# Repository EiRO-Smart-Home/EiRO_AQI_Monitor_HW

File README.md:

# AQI monitor

This project is a developement board based on a MGM260PD32VNA2 Module from SiliconLabs, SEN5x series sensors and with support for ePaper and other SPI based displays.
This board has been realized for the lack of available options that would satisfy our need in therms of a good air quality sensor. As for most commercial solutions are expensive, or they lack some features, such as Matter connectivity or some types of enviromental sensing. Most of the time they detect only PM2.5 and not PM10 and some do not include VOCs. 
Our targets of sensing values are the followings.
- Temperature
- Humidity
- PM 1.0, PM 2.5, PM 4, PM10
- VOC (index)
- CO2 
- NOx
- Formaldehyde 
- Overall AQI index (calculated)
  
Most of the sensing can be done using SEN55 and two addittional sensors for Formaldehyde and CO2. A SEN69C can also be used, but VCC on the connector is 5V and newer SEN6x are 3.3V powered, so the board has to be modified.

An advantage of using Matter as the default connectivity standard, is the ease of integrating it in any smart home (with also a Thread Border Router). There is no need for vendor specific applications, as all the data will be managed by Matter. This means there is no need for subscription and the device is completely local.

## Hardware Features

 - MGM260 SoM
   * BLE 5.4 Support 
   * Zigbee 3.0 and up
   * OpenThread
   * ARM Cortex M33 @ 80 MHz
   * 3.2MB Flash + 512kB RAM
   * Matrix Vector Processor for ML
 - SHT41 Temp. and Humidity Sensor
 - JTAG-SWD-9 connector
 - SPI expansion 4x2 1.27mm pitch
 - SPI connection for external display 
 - I2C expansion for external SEN5x series sensor node
 - USB-C for power and serial communication

## PICTURES

## LICENSE

Copyright Francesco Salmaso - EiRO.tech 2025-2026
This source describes Open Hardware and is licensed under the CERN-
OHL-S v2.
You may redistribute and modify this source and make products using it
under the terms of the CERN-OHL-S v2
(https://ohwr.org/cern ohl s v2.txt ).
This source is distributed WITHOUT ANY EXPRESS OR IMPLIED
WARRANTY, INCLUDING OF MERCHANTABILITY, SATISFACTORY
QUALITY AND FITNESS FOR A PARTICULAR PURPOSE. Please see
the CERN-OHL-S v2 for applicable conditions.
Source location: https://github.com/EiRO-Smart-Home/EiRO_AQI_Monitor_HW
As per CERN-OHL-S v2 section 4, should You produce hardware based
on this source, You must where practicable maintain the Source Location
visible on the external case of the EiRO AQI Monitor or other products you make using
this source.

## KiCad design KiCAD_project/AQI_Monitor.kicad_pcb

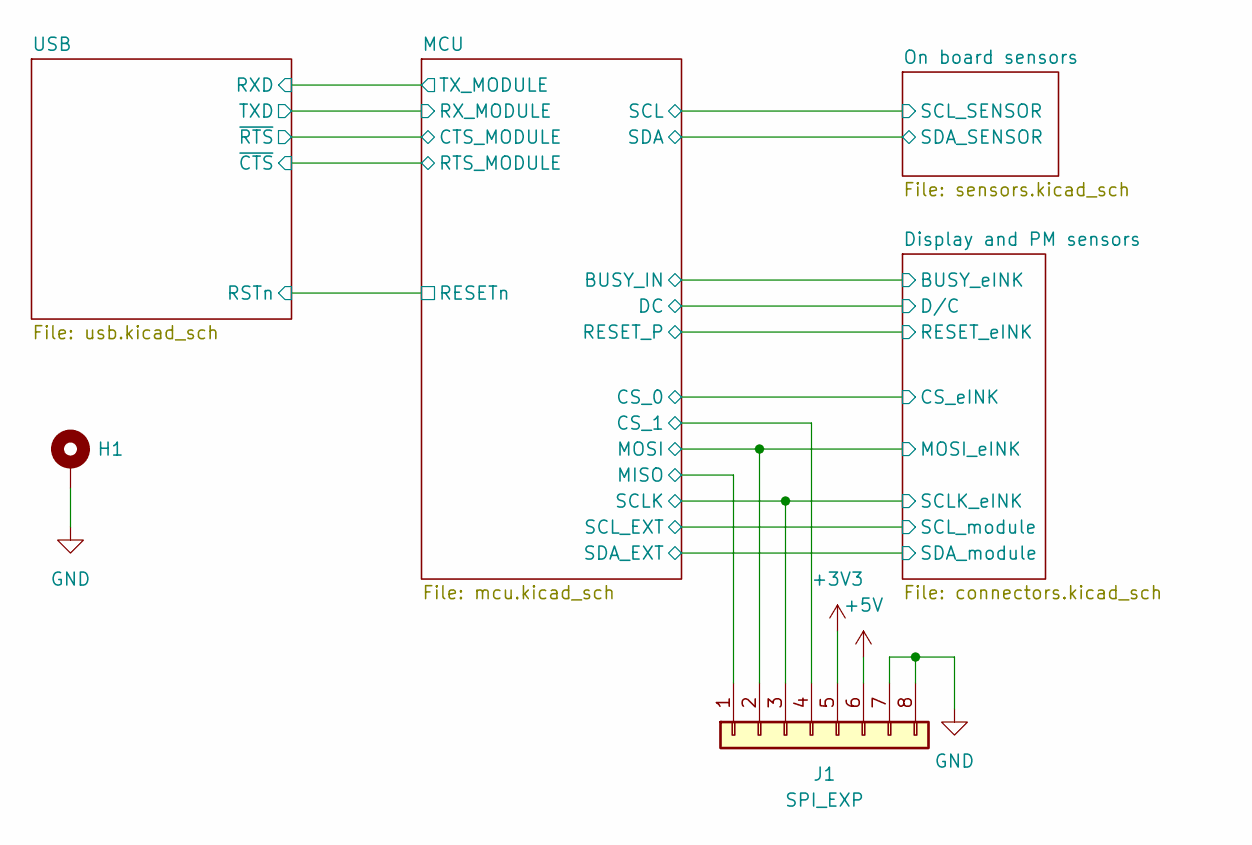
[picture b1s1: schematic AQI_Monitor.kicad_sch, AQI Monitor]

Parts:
H1: MountingHole_Pad; MountingHole_2.7mm_M2.5_DIN965_Pad
J1: SPI_EXP; PinHeader_2x04_P1.27mm_Vertical_SMD

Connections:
+3V3: J1.5; also elsewhere on the board
+5V: J1.6; also elsewhere on the board
/Display and PM sensors/MOSI_eINK: J1.2; also elsewhere on the board
/Display and PM sensors/SCLK_eINK: J1.3; also elsewhere on the board
/MCU/CS_1: J1.4; also elsewhere on the board
/MCU/MISO: J1.1; also elsewhere on the board
GND: H1.1, J1.7, J1.8; also elsewhere on the board

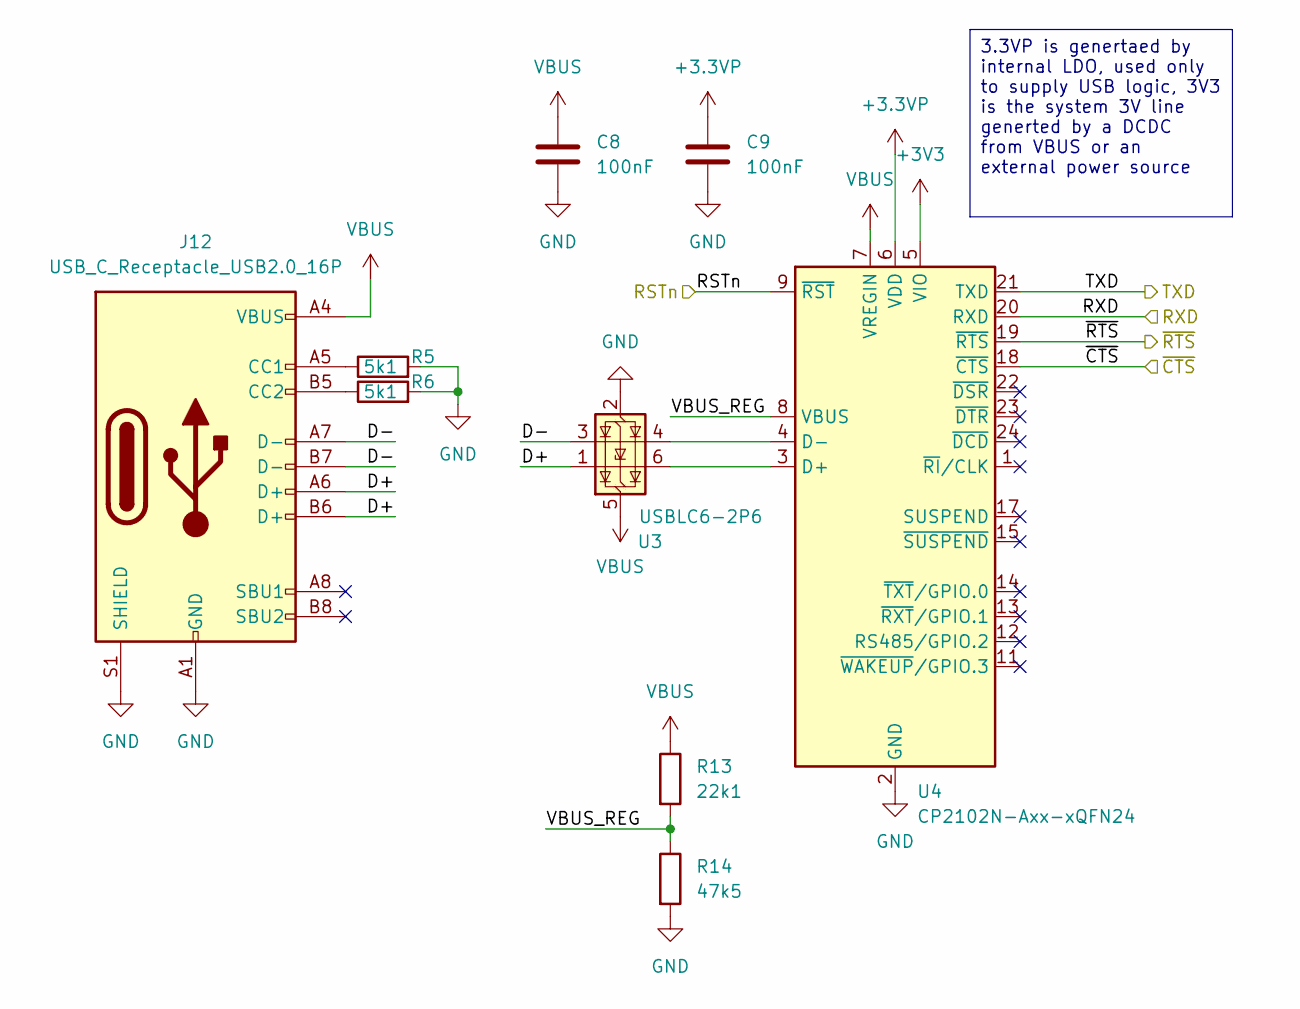
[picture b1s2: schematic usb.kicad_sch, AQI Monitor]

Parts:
C8, C9: 100nF; C_0603_1608Metric_Pad1.08x0.95mm_HandSolder
J12: USB_C_Receptacle_USB2.0_16P; USB_C_Receptacle_JAE_DX07S016JA1R1500
R5, R6: 5k1; R_0603_1608Metric_Pad0.98x0.95mm_HandSolder
R13: 22k1; R_0603_1608Metric_Pad0.98x0.95mm_HandSolder
R14: 47k5; R_0603_1608Metric_Pad0.98x0.95mm_HandSolder
U3: USBLC6-2P6; SOT-666
U4: CP2102N-Axx-xQFN24; QFN-24-1EP_4x4mm_P0.5mm_EP2.6x2.6mm

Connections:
+3.3VP: C9.1, U4.6 (VDD)
+3V3: U4.5 (VIO); also elsewhere on the board
/MCU/CTS_MODULE: U4.19 (~RTS); also elsewhere on the board
/MCU/RESETn: U4.9 (~RST); also elsewhere on the board
/MCU/RTS_MODULE: U4.18 (~CTS); also elsewhere on the board
/MCU/RX_MODULE: U4.21 (TXD); also elsewhere on the board
/MCU/TX_MODULE: U4.20 (RXD); also elsewhere on the board
/USB/D+: J12.A6 (D+), J12.B6 (D+), U3.1 (I/O1)
/USB/D-: J12.A7 (D-), J12.B7 (D-), U3.3 (I/O2)
/USB/VBUS_REG: R13.2, R14.1, U4.8 (VBUS)
GND: C8.2, C9.2, J12.A1 (GND), J12.A12 (GND), J12.B1 (GND), J12.B12 (GND), J12.S1 (SHIELD), R5.2, R6.2, R14.2, U3.2 (GND), U4.2 (GND), U4.25 (GND); also elsewhere on the board
unnamed: J12.A5 (CC1), R5.1
unnamed: J12.B5 (CC2), R6.1
unnamed: U3.6 (I/O1), U4.3 (D+)
unnamed: U3.4 (I/O2), U4.4 (D-)
VBUS: C8.1, J12.A4 (VBUS), J12.A9 (VBUS), J12.B4 (VBUS), J12.B9 (VBUS), R13.1, U3.5 (VBUS), U4.7 (VREGIN); also elsewhere on the board

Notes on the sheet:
3.3VP is genertaed by internal LDO, used only to supply USB logic, 3V3 is the system 3V line generted by a DCDC from VBUS or an external power source

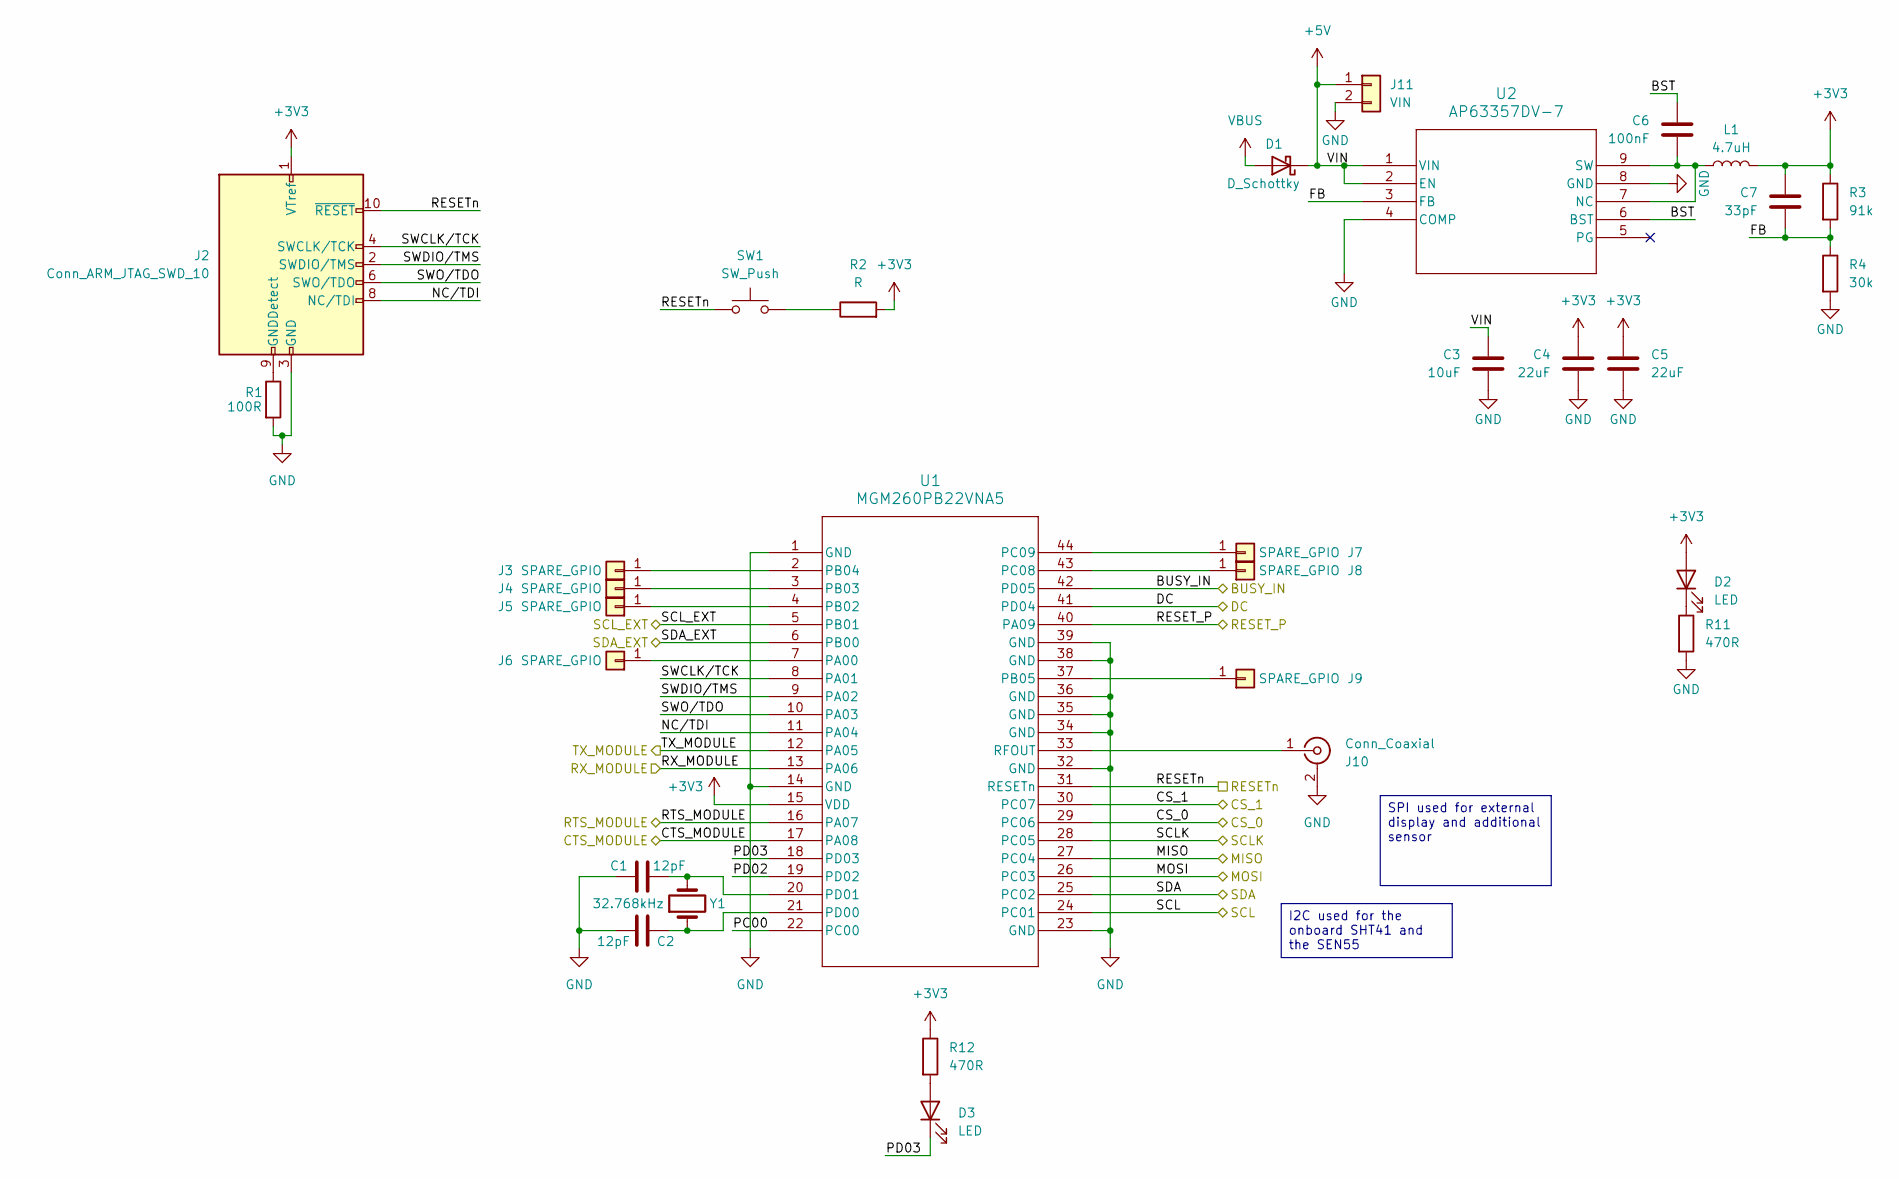
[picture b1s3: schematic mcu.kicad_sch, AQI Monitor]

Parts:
C1, C2: 12pF; C_0603_1608Metric_Pad1.08x0.95mm_HandSolder
C3: 10uF; C_0805_2012Metric_Pad1.18x1.45mm_HandSolder
C4, C5: 22uF; C_0805_2012Metric_Pad1.18x1.45mm_HandSolder
C6: 100nF; C_0603_1608Metric_Pad1.08x0.95mm_HandSolder
C7: 33pF; C_0603_1608Metric_Pad1.08x0.95mm_HandSolder
D1: D_Schottky; D_SMA
D2, D3: LED; D_0603_1608Metric_Pad1.05x0.95mm_HandSolder
J2: Conn_ARM_JTAG_SWD_10; PinHeader_2x05_P1.27mm_Vertical_SMD
J3, J4, J5, J6, J7, J8, J9: SPARE_GPIO; SolderWirePad_1x01_SMD_1x2mm
J10: Conn_Coaxial; U.FL_Hirose_U.FL-R-SMT-1_Vertical
J11: VIN; PinSocket_1x02_P2.54mm_Vertical
L1: 4.7uH; L_1210_3225Metric_Pad1.42x2.65mm_HandSolder
R1: 100R; R_0603_1608Metric_Pad0.98x0.95mm_HandSolder
R2: R; R_0603_1608Metric_Pad0.98x0.95mm_HandSolder
R3: 91k; R_0603_1608Metric_Pad0.98x0.95mm_HandSolder
R4: 30k; R_0603_1608Metric_Pad0.98x0.95mm_HandSolder
R11, R12: 470R; R_0603_1608Metric_Pad0.98x0.95mm_HandSolder
SW1: SW_Push; SW_SPST_PTS810
U1: MGM260PB22VNA5; MODULE_xGM260P_SIL
U2: AP63357DV-7; V-DFN3020-13_DIO
Y1: 32.768kHz; Crystal_SMD_MicroCrystal_CC8V-T1A-2Pin_2.0x1.2mm_HandSolder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

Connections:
+3V3: C4.1, C5.1, C7.1, D2.2 (A), J2.1 (VTref), L1.2, R2.2, R3.1, R12.1, U1.15 (VDD); also elsewhere on the board
+5V: C3.1, D1.1 (K), J11.1, U2.1 (VIN), U2.2 (EN); also elsewhere on the board
/Display and PM sensors/BUSY_eINK: U1.42 (PD05); also elsewhere on the board
/Display and PM sensors/CS_eINK: U1.29 (PC06); also elsewhere on the board
/Display and PM sensors/D/C: U1.41 (PD04); also elsewhere on the board
/Display and PM sensors/MOSI_eINK: U1.26 (PC03); also elsewhere on the board
/Display and PM sensors/RESET_eINK: U1.40 (PA09); also elsewhere on the board
/Display and PM sensors/SCLK_eINK: U1.28 (PC05); also elsewhere on the board
/Display and PM sensors/SCL_module: U1.5 (PB01); also elsewhere on the board
/Display and PM sensors/SDA_module: U1.6 (PB00); also elsewhere on the board
/MCU/BST: C6.1, U2.6 (BST)
/MCU/CS_1: U1.30 (PC07); also elsewhere on the board
/MCU/CTS_MODULE: U1.17 (PA08); also elsewhere on the board
/MCU/FB: C7.2, R3.2, R4.1, U2.3 (FB)
/MCU/MISO: U1.27 (PC04); also elsewhere on the board
/MCU/PC00: U1.22 (PC00)
/MCU/PD02: U1.19 (PD02)
/MCU/PD03: D3.1 (K), U1.18 (PD03)
/MCU/RESETn: J2.10 (~RESET), SW1.1, U1.31 (RESETn); also elsewhere on the board
/MCU/RTS_MODULE: U1.16 (PA07); also elsewhere on the board
/MCU/RX_MODULE: U1.13 (PA06); also elsewhere on the board
/MCU/SCL: U1.24 (PC01); also elsewhere on the board
/MCU/SDA: U1.25 (PC02); also elsewhere on the board
/MCU/TX_MODULE: U1.12 (PA05); also elsewhere on the board
GND: C1.1, C2.2, C3.2, C4.2, C5.2, J2.3 (GND), J2.5 (GND), J10.2 (Ext), J11.2, R1.2, R4.2, R11.2, U1.1 (GND), U1.14 (GND), U1.23 (GND), U1.32 (GND), U1.34 (GND), U1.35 (GND), U1.36 (GND), U1.38 (GND), U1.39 (GND), U2.4 (COMP), U2.8 (GND); also elsewhere on the board
unnamed: D2.1 (K), R11.1
unnamed: D3.2 (A), R12.2
unnamed: J2.9 (GNDDetect), R1.1
unnamed: J3.1, U1.2 (PB04)
unnamed: J4.1, U1.3 (PB03)
unnamed: J5.1, U1.4 (PB02)
unnamed: J6.1, U1.7 (PA00)
unnamed: J7.1, U1.44 (PC09)
unnamed: J8.1, U1.43 (PC08)
unnamed: J9.1, U1.37 (PB05)
unnamed: J10.1 (In), U1.33 (RFOUT)
unnamed: R2.1, SW1.2
unnamed: C2.1, U1.21 (PD00), Y1.1
unnamed: C1.2, U1.20 (PD01), Y1.2
unnamed: C6.2, L1.1, U2.7 (NC), U2.9 (SW)
VBUS: D1.2 (A); also elsewhere on the board

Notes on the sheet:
I2C used for the onboard SHT41 and the SEN55
SPI used for external display and additional sensor

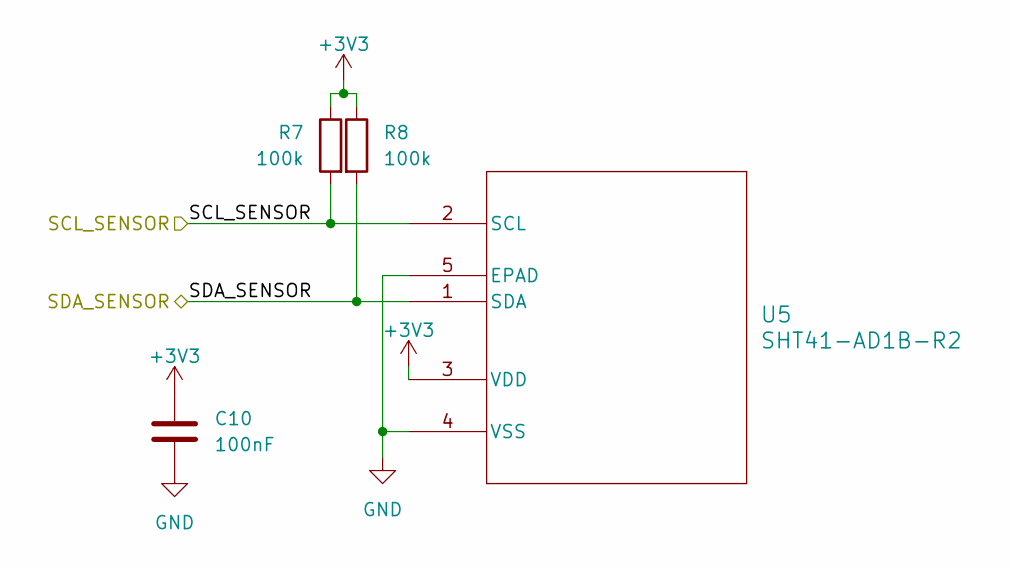
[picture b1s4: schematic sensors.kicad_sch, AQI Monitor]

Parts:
C10: 100nF; C_0603_1608Metric_Pad1.08x0.95mm_HandSolder
R7, R8: 100k; R_0603_1608Metric_Pad0.98x0.95mm_HandSolder
U5: SHT41-AD1B-R2; DFN4_SHT41_SEN

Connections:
+3V3: C10.1, R7.1, R8.1, U5.3 (VDD); also elsewhere on the board
/MCU/SCL: R7.2, U5.2 (SCL); also elsewhere on the board
/MCU/SDA: R8.2, U5.1 (SDA); also elsewhere on the board
GND: C10.2, U5.4 (VSS), U5.5 (EPAD); also elsewhere on the board

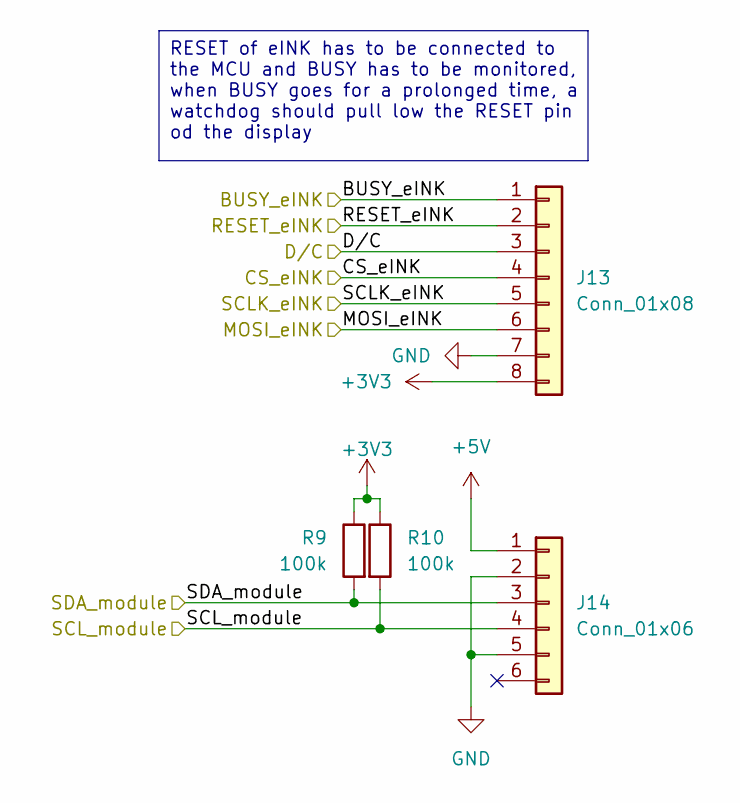
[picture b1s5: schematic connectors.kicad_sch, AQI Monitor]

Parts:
J13: Conn_01x08; JST_GH_BM08B-GHS-TBT_1x08-1MP_P1.25mm_Vertical
J14: Conn_01x06; JST_GH_BM06B-GHS-TBT_1x06-1MP_P1.25mm_Vertical
R9, R10: 100k; R_0603_1608Metric_Pad0.98x0.95mm_HandSolder

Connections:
+3V3: J13.8, R9.1, R10.1; also elsewhere on the board
+5V: J14.1; also elsewhere on the board
/Display and PM sensors/BUSY_eINK: J13.1; also elsewhere on the board
/Display and PM sensors/CS_eINK: J13.4; also elsewhere on the board
/Display and PM sensors/D/C: J13.3; also elsewhere on the board
/Display and PM sensors/MOSI_eINK: J13.6; also elsewhere on the board
/Display and PM sensors/RESET_eINK: J13.2; also elsewhere on the board
/Display and PM sensors/SCLK_eINK: J13.5; also elsewhere on the board
/Display and PM sensors/SCL_module: J14.4, R10.2; also elsewhere on the board
/Display and PM sensors/SDA_module: J14.3, R9.2; also elsewhere on the board
GND: J13.7, J14.2, J14.5; also elsewhere on the board

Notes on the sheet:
RESET of eINK has to be connected to the MCU and BUSY has to be monitored, when BUSY goes for a prolonged time, a watchdog should pull low the RESET pin od the display

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
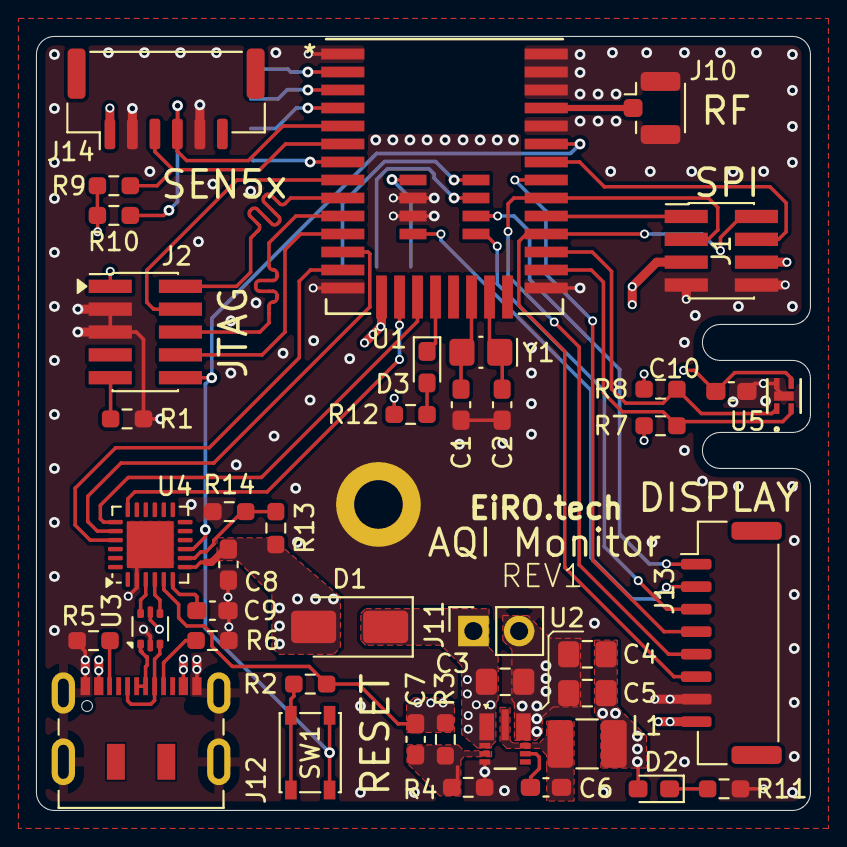
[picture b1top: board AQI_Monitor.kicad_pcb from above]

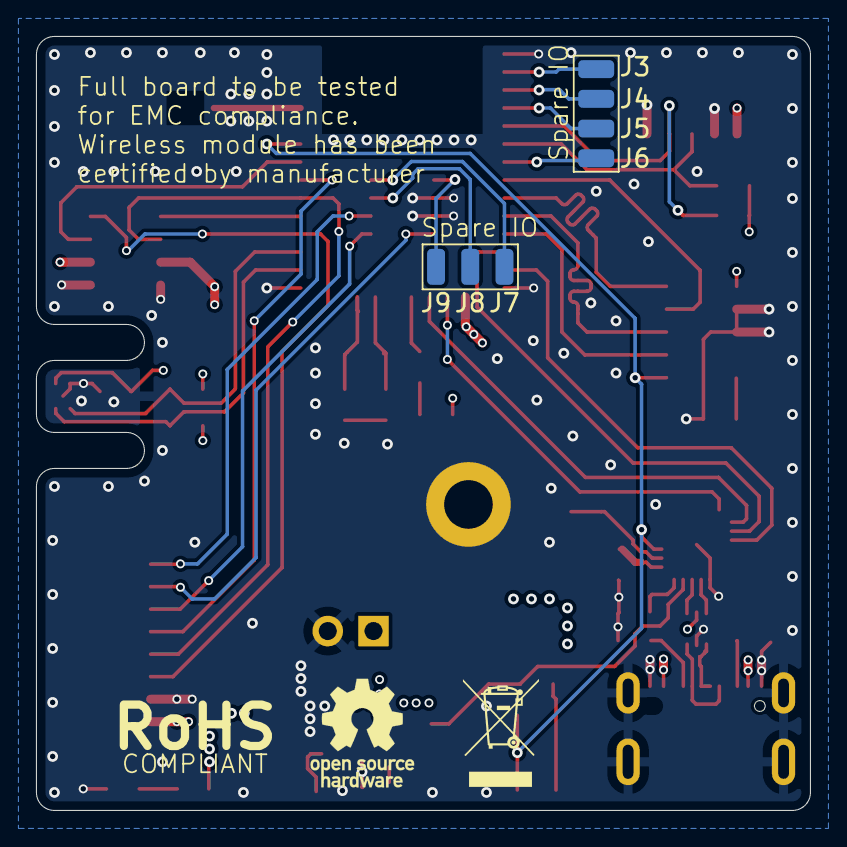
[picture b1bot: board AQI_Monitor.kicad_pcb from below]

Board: 4 copper layers, 43.0 x 43.0 mm, 50 parts (7 on the bottom side), 51 nets.

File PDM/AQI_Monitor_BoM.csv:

Id;Designator;Footprint;Quantity;Designation;Supplier and ref;;
1;R14;R_0603_1608Metric_Pad0.98x0.95mm_HandSolder;1;47k5;;v;x
2;C7;C_0603_1608Metric_Pad1.08x0.95mm_HandSolder;1;33pF;;v;x
3;R6,R5;R_0603_1608Metric_Pad0.98x0.95mm_HandSolder;2;5k1;;v;x
4;C3;C_0805_2012Metric_Pad1.18x1.45mm_HandSolder;1;10uF;;v;x
5;J14;JST_GH_BM06B-GHS-TBT_1x06-1MP_P1.25mm_Vertical;1;Conn_01x06;;ok;
6;R12,R11;R_0603_1608Metric_Pad0.98x0.95mm_HandSolder;2;470R;;v;x
7;C10,C8,C9,C6;C_0603_1608Metric_Pad1.08x0.95mm_HandSolder;4;100nF;;v;x
8;C1,C2;C_0603_1608Metric_Pad1.08x0.95mm_HandSolder;2;12pF;;v;x
9;D1;D_SMA;1;D_Schottky;;v;x
10;U4;QFN-24-1EP_4x4mm_P0.5mm_EP2.6x2.6mm;1;CP2102N-Axx-xQFN24;;v;x
11;SW1;SW_SPST_PTS810;1;SW_Push;;v;x
12;R8,R7,R9,R10;R_0603_1608Metric_Pad0.98x0.95mm_HandSolder;4;100k;;v;x
13;C4,C5;C_0805_2012Metric_Pad1.18x1.45mm_HandSolder;2;22uF;;v;x
14;J12;USB_C_Receptacle_JAE_DX07S016JA1R1500;1;USB_C_Receptacle_USB2.0_16P;;ok;
15;U1;MODULE_xGM260P_SIL;1;MGM260PB22VNA5;;v;xxx
16;J1;PinHeader_2x04_P1.27mm_Vertical_SMD;1;SPI_EXP;;v;x
17;R1;R_0603_1608Metric_Pad0.98x0.95mm_HandSolder;1;100R;;v;x
18;D3,D2;D_0603_1608Metric_Pad1.05x0.95mm_HandSolder;2;LED;;v;xx
19;R3;R_0603_1608Metric_Pad0.98x0.95mm_HandSolder;1;91k;;v;x
20;U2;V-DFN3020-13_DIO;1;AP63357DV-7;;ok;
21;J11;PinSocket_1x02_P2.54mm_Vertical;1;VIN;;ok;
22;J13;JST_GH_BM08B-GHS-TBT_1x08-1MP_P1.25mm_Vertical;1;Conn_01x08;;v;x
23;L1;L_1210_3225Metric_Pad1.42x2.65mm_HandSolder;1;4.7uH;;v;x
24;Y1;Crystal_SMD_MicroCrystal_CC8V-T1A-2Pin_2.0x1.2mm_HandSoldering;1;32.768kHz;;v;x
25;J2;PinHeader_2x05_P1.27mm_Vertical_SMD;1;Conn_ARM_JTAG_SWD_10;;v;x
26;R4;R_0603_1608Metric_Pad0.98x0.95mm_HandSolder;1;30k;;v;x
27;R2;R_0603_1608Metric_Pad0.98x0.95mm_HandSolder;1;R;;ok;
28;U3;SOT-666;1;USBLC6-2P6;;v;x
29;R13;R_0603_1608Metric_Pad0.98x0.95mm_HandSolder;1;22k1;;v;x
30;U5;DFN4_SHT41_SEN;1;SHT41-AD1B-R2;;ok;
31;J10;U.FL_Hirose_U.FL-R-SMT-1_Vertical;1;Conn_Coaxial;;v;x
32;J8,J4,J3,J6,J9,J5,J7;SolderWirePad_1x01_SMD_1x2mm;7;SPARE_GPIO;;v;x

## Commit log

2026-02-28 First commit
    Initial KiCAD files, gerber and schematic of the AQI monitor (already produced)
2026-03-23 Updated files, added license
    Updated the Readme, inserted a new image, fixed the preexisting images (converted from .heic to .jpg). Added license.
